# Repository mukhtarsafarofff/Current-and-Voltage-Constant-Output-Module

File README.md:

(ENG) I have added 2N3055 to enlarge current the Current at LM723.

(DEU)

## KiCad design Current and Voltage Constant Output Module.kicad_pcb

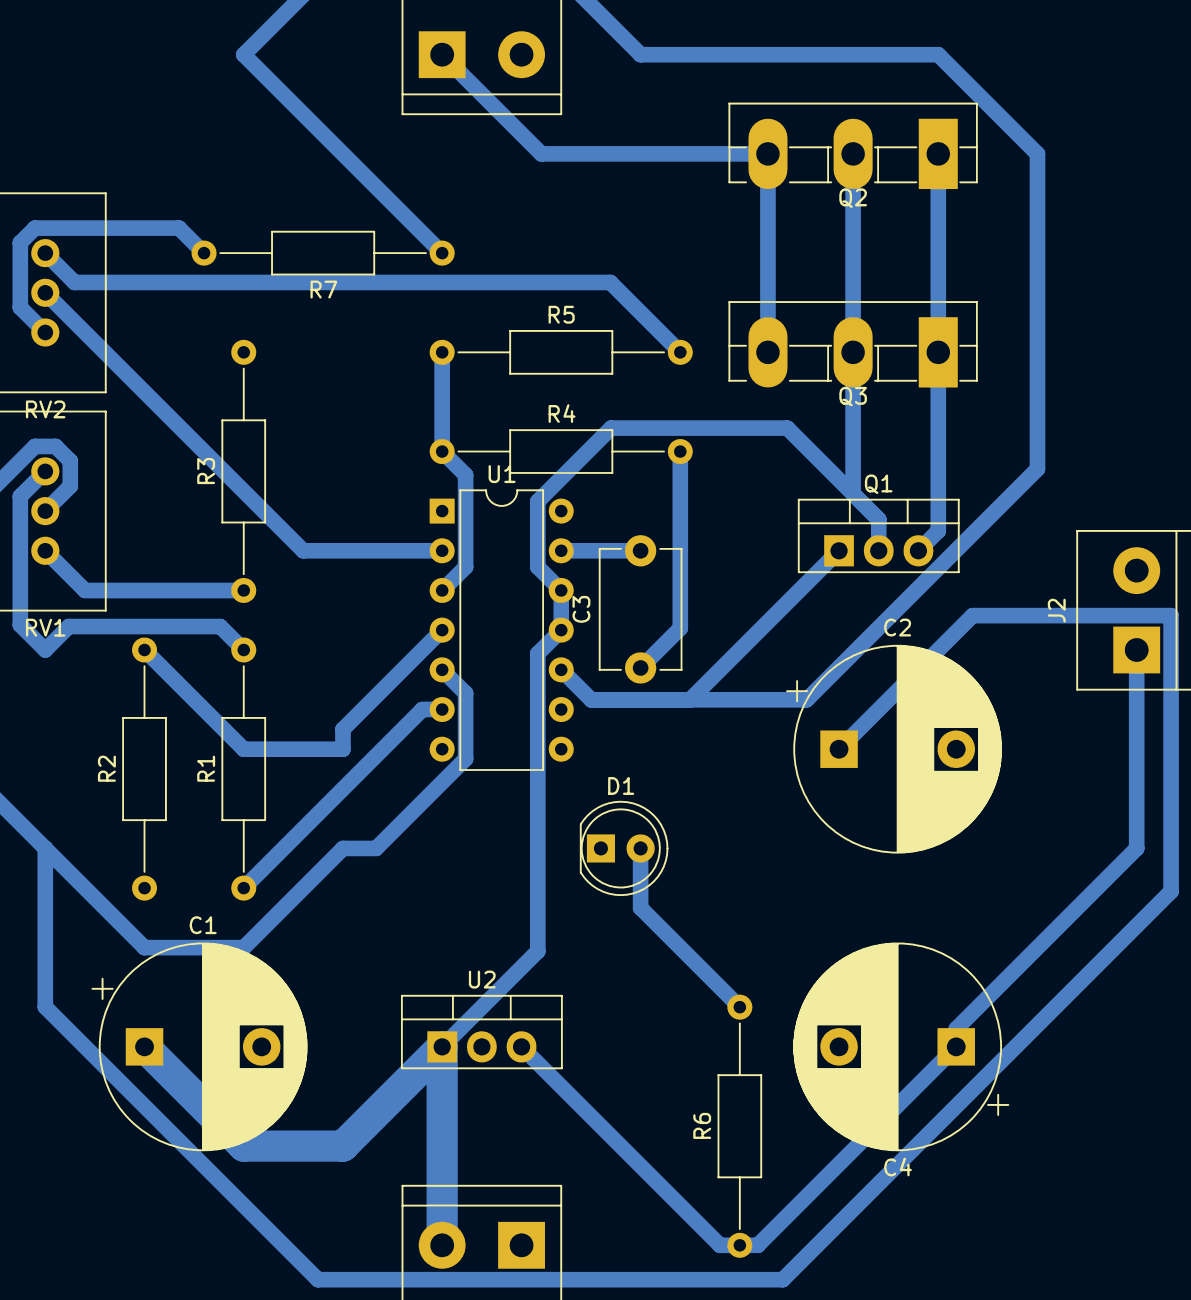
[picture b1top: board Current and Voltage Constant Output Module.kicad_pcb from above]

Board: 2 copper layers, 22 parts (0 on the bottom side), 18 nets.

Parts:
C1, C2: 1uF; CP_Radial_D13.0mm_P7.50mm
C3: 100nF; C_Disc_D7.5mm_W5.0mm_P7.50mm
C4: 100uF; CP_Radial_D13.0mm_P7.50mm
D1: LED; LED_D5.0mm_Clear
J1: INPUT Voltage; TerminalBlock_bornier-2_P5.08mm
J2: FAN; TerminalBlock_bornier-2_P5.08mm
J3: OUTPUT Voltage; TerminalBlock_bornier-2_P5.08mm
Q1: TIP41C; TO-220-3_Vertical
Q2, Q3: 2SD1047; TO-3PB-3_Vertical
R1: 1K; R_Axial_DIN0207_L6.3mm_D2.5mm_P15.24mm_Horizontal
R2: 2,2K; R_Axial_DIN0207_L6.3mm_D2.5mm_P15.24mm_Horizontal
R3, R7: 680R; R_Axial_DIN0207_L6.3mm_D2.5mm_P15.24mm_Horizontal
R4: 68K; R_Axial_DIN0207_L6.3mm_D2.5mm_P15.24mm_Horizontal
R5: 470R; R_Axial_DIN0207_L6.3mm_D2.5mm_P15.24mm_Horizontal
R6: 330R; R_Axial_DIN0207_L6.3mm_D2.5mm_P15.24mm_Horizontal
RV1: 10K; Potentiometer_Vishay_148-149_Single_Horizontal
RV2: 1K; Potentiometer_Vishay_148-149_Single_Horizontal
U1: LM723_DIP14; DIP-14_W7.62mm
U2: LM7812; TO-220-3_Vertical

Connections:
Earth: C1.2, C2.2, C4.2, D1.1 (K), J1.1, J2.2, J3.2, R2.1, R3.2, U1.7 (V-), U2.2 (GND)
I Sense: R4.1, R5.1, U1.3 (CSEN)
unnamed: C3.1, R4.2
unnamed: D1.2 (A), R6.2
unnamed: C4.1, J2.1, R6.1, U2.3 (VO)
unnamed: J3.1, Q2.3 (E), Q3.3 (E)
unnamed: Q1.3 (E), Q2.1 (B), Q3.1 (B)
unnamed: R1.2, RV1.1
unnamed: R3.1, RV1.3
unnamed: R5.2, RV2.1
unnamed: R7.2, RV2.3
unnamed: C2.1, RV1.2, U1.5 (+)
unnamed: R2.2, U1.4 (-)
unnamed: C3.2, U1.13 (FC)
unnamed: RV2.2, U1.2 (ILIM)
unnamed: R1.1, U1.6 (VREF)
VCC: C1.1, J1.2, Q1.2 (C), Q2.2 (C), Q3.2 (C), U1.11 (VC), U1.12 (V+), U2.1 (VI)
Vout: Q1.1 (B), R7.1, U1.10 (Vout)

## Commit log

2024-03-21 Current and Voltage module is accomplished
2024-03-23 current module is restored
